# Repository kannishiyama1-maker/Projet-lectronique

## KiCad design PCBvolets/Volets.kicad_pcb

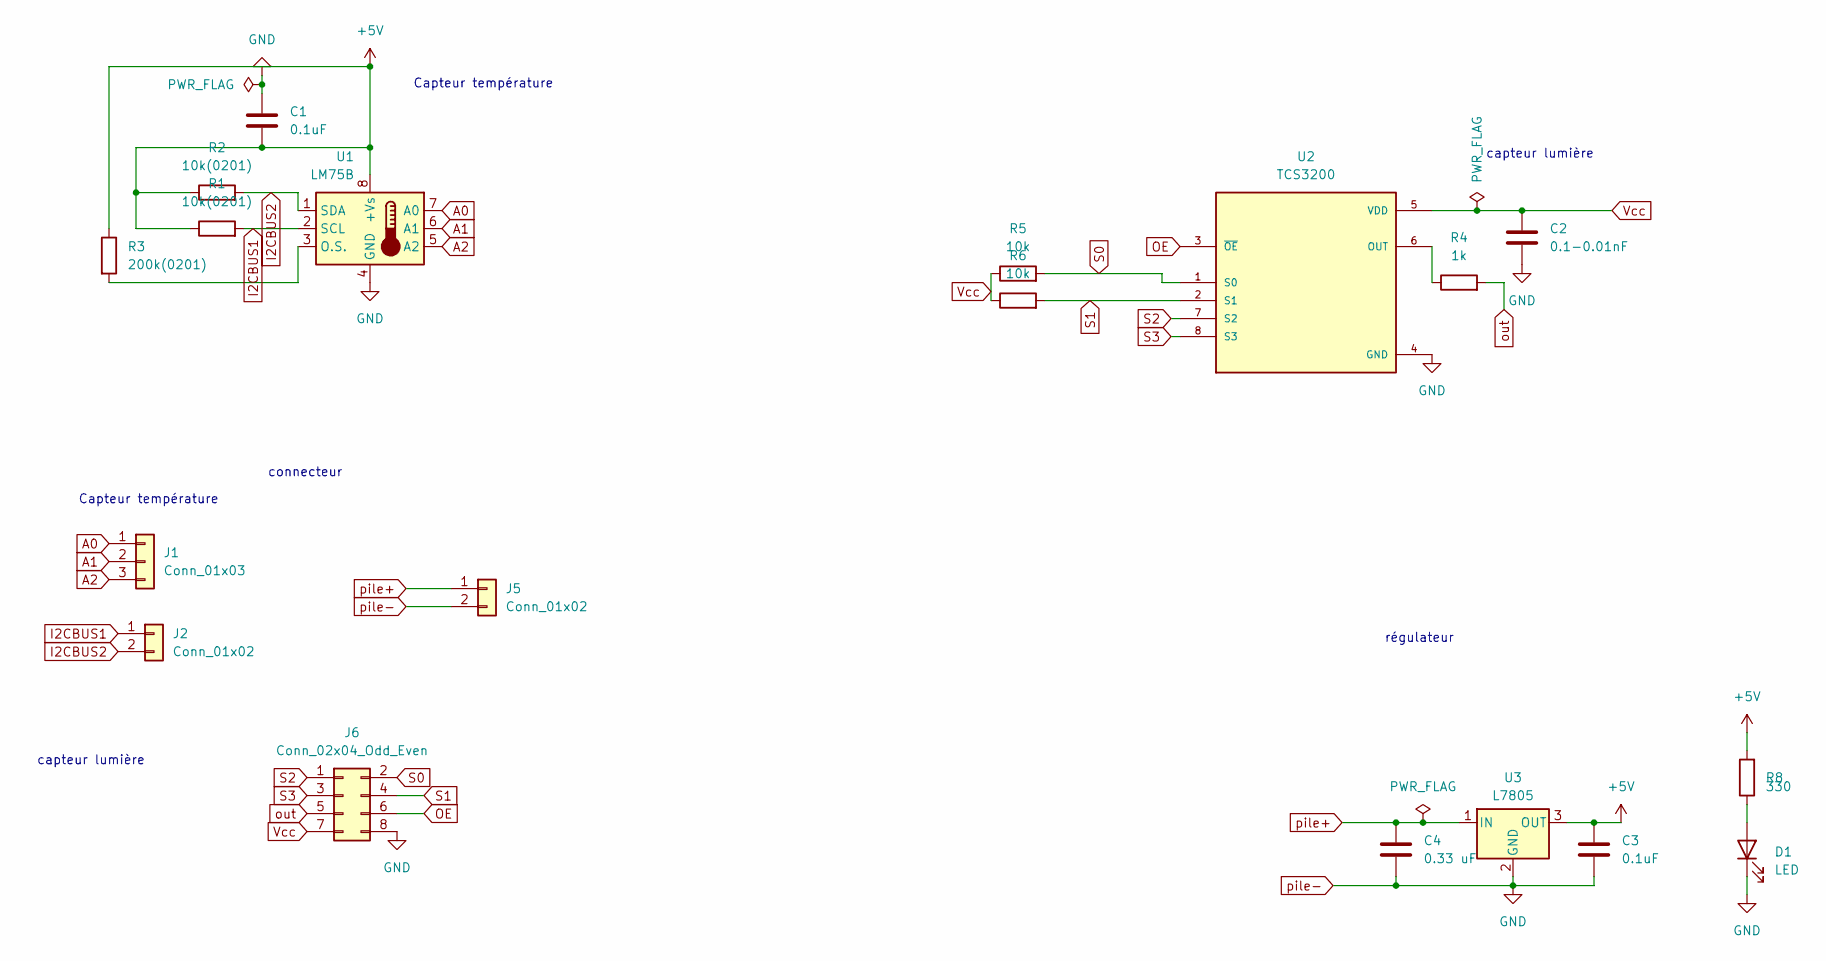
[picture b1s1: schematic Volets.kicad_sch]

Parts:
C1, C3: 0.1uF; C_1206_3216Metric_Pad1.33x1.80mm_HandSolder
C2: 0.1-0.01nF; C_1206_3216Metric_Pad1.33x1.80mm_HandSolder
C4: 0.33 uF; C_1206_3216Metric_Pad1.33x1.80mm_HandSolder
D1: LED; R_1206_3216Metric_Pad1.30x1.75mm_HandSolder
J1: Conn_01x03; PinSocket_1x03_P1.27mm_Vertical
J2, J5: Conn_01x02; PinSocket_1x02_P1.27mm_Vertical
J6: Conn_02x04_Odd_Even; PinSocket_2x04_P1.27mm_Vertical_SMD
R1, R2: 10k(0201); R_1206_3216Metric_Pad1.30x1.75mm_HandSolder
R3: 200k(0201); R_1206_3216Metric_Pad1.30x1.75mm_HandSolder
R4: 1k; R_1206_3216Metric_Pad1.30x1.75mm_HandSolder
R5, R6: 10k; R_1206_3216Metric_Pad1.30x1.75mm_HandSolder
R8: 330; R_1206_3216Metric_Pad1.30x1.75mm_HandSolder
U1: LM75B; capteur LM75B
U2: TCS3200; SOIC127P600X175-8N
U3: L7805; L780(

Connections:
+5V: C1.2, C3.1, R1.1, R2.1, R3.1, R8.2, U1.8 (+Vs), U3.3 (OUT)
A0: J1.1, U1.7 (A0)
A1: J1.2, U1.6 (A1)
A2: J1.3, U1.5 (A2)
I2CBUS1: J2.1, R1.2, U1.2 (SCL)
I2CBUS2: J2.2, R2.2, U1.1 (SDA)
unnamed: D1.2 (A), R8.1
unnamed: R3.2, U1.3 (O.S.)
unnamed: R4.1, U2.6 (OUT)
OE: J6.6, U2.3 (~OE)
S0: J6.2, R5.2, U2.1 (S0)
S1: J6.4, R6.2, U2.2 (S1)
S2: J6.1, U2.7 (S2)
S3: J6.3, U2.8 (S3)
Vcc: C2.1, J6.7, R5.1, R6.1, U2.5 (VDD)
out: J6.5, R4.2
pile+: C4.1, J5.1, U3.1 (IN)
pile-: C1.1, C2.2, C3.2, C4.2, D1.1 (K), J5.2, J6.8, U1.4 (GND), U2.4 (GND), U3.2 (GND)

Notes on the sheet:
régulateur
capteur lumière
Capteur température
connecteur

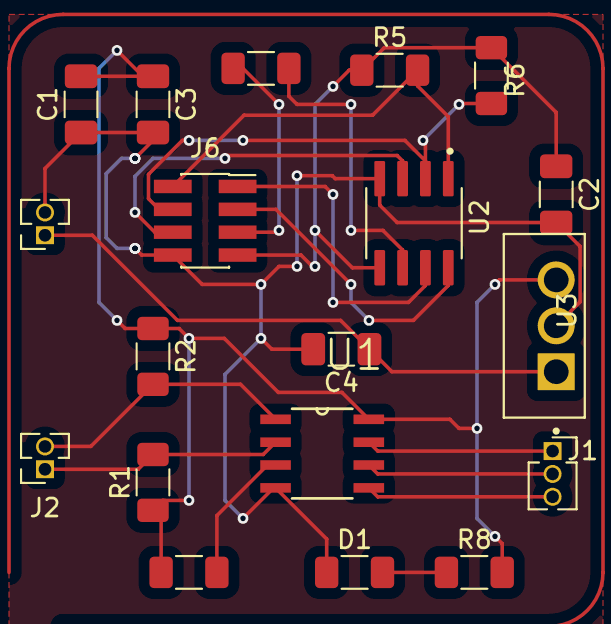
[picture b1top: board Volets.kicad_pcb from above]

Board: 2 copper layers, 19 parts (0 on the bottom side), 18 nets.

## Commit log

2026-02-05 Create cahier_des_charges
2026-02-12 Mise à jour
2026-02-19 Mise à jour du schéma Volets
